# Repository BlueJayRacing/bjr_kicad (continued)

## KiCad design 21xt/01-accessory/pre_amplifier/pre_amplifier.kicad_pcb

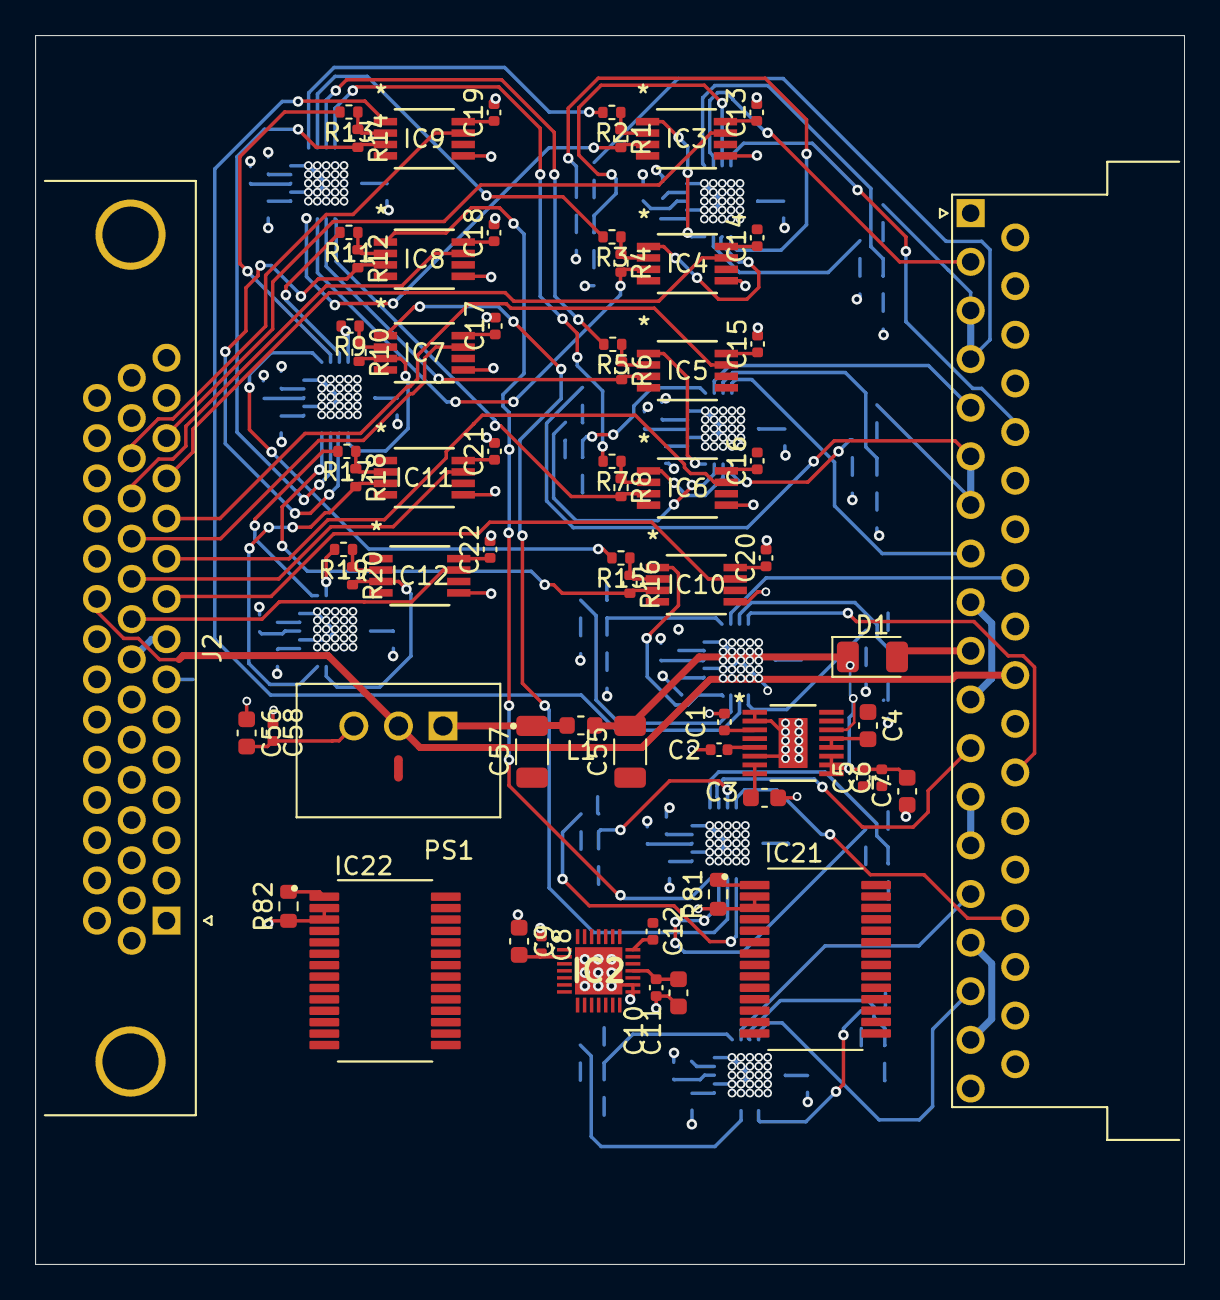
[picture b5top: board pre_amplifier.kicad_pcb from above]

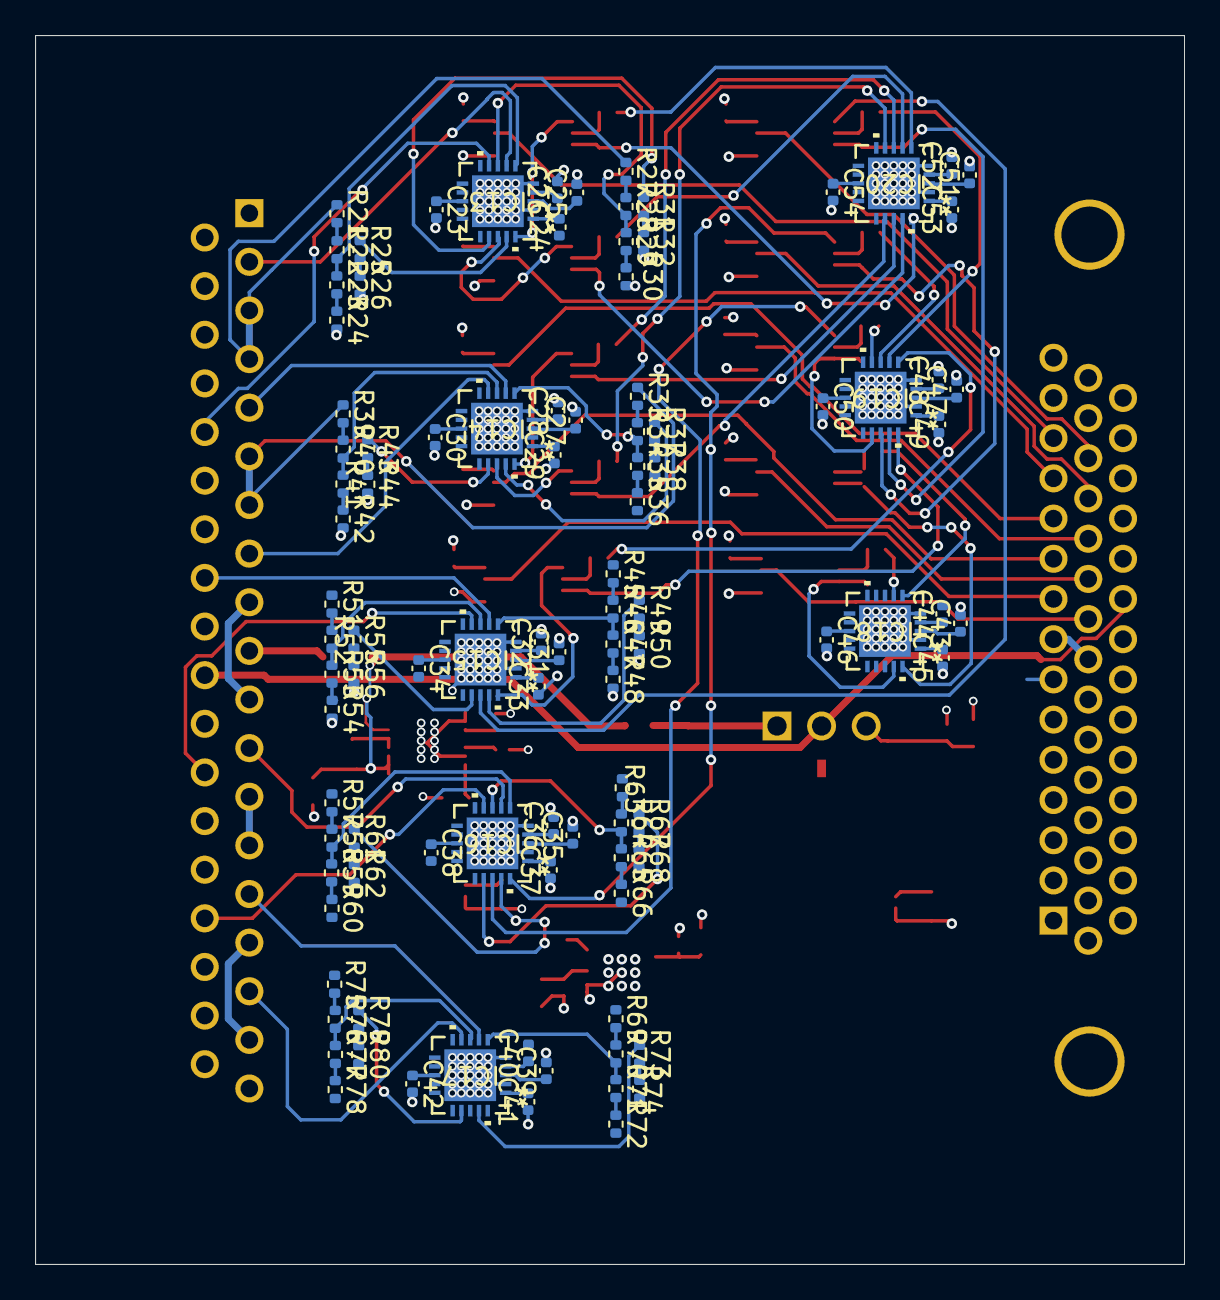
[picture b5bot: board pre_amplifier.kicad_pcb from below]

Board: 4 copper layers, 65.4 x 70.0 mm, 168 parts (100 on the bottom side), 187 nets.

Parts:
C1: 1u; C_0402_1005Metric
C2, C5, C6, C8, C10, C12, C58: 0.1u; C_0402_1005Metric
C3, C4, C7, C9, C11, C56: 10u; C_0603_1608Metric
C13, C14, C15, C16, C17, C18, C19, C20, C21, C22: 0.1uF; C_0402_1005Metric
C23, C26, C28, C30, C32, C34, C36, C38, C40, C42, C44, C46, C48, C50, C52, C54: 1uF; C_0402_1005Metric
C24, C25, C27, C29, C31, C33, C35, C37, C39, C41, C43, C45, C47, C49, C51, C53: 10nF; C_0402_1005Metric
C55, C57: 4.7u; C_1206_3216Metric
D1: D_Schottky; D_1206_3216Metric
IC1: LT6658AHMSE-5#PBF; LT6658AHMSE-2.5-PBF
IC2: AD5679RBCPZ-1; QFN40P400X400X100-29N-D
IC3, IC4, IC5, IC6, IC7, IC8, IC9, IC10, IC11, IC12: INA827AIDGKR
IC13, IC14, IC15, IC16, IC17, IC18, IC19, IC20: MAX14774ATP+; MAX14774ATP_
IC21, IC22: MAX7301AAI+; SOP65P777X199-28N
J1: Conn_02x19_Counter_Clockwise; DSUB-37_Female_Horizontal_P2.77x2.54mm_EdgePinOffset9.40mm
J2: Conn_02x23_Counter_Clockwise; DSUB-44-HD_Female_Horizontal_P2.29x1.98mm_EdgePinOffset3.03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
L1: 10u; L_0603_1608Metric
NT1: NetTie_2; NetTie-2_SMD_Pad0.5mm
PS1: P7805B-500; CONV_P7805B-500
R1, R4, R6, R8, R10, R12, R14, R16, R18, R20: 35; R_0402_1005Metric
R2, R3, R5, R7, R9, R11, R13, R15, R17, R19: R; R_0402_1005Metric
R21, R23, R25, R27, R29, R31, R33, R35, R37, R39, R41, R43, R45, R47, R49, R51, R53, R55, R57, R59, R61, R63, R65, R67, R69, R71, R73, R75, R77, R79: 330; R_0402_1005Metric
R22, R24, R26, R28, R30, R32, R34, R36, R38, R40, R42, R44, R46, R48, R50, R52, R54, R56, R58, R60, R62, R64, R66, R68, R70, R72, R74, R76, R78, R80: 20; R_0402_1005Metric
R81, R82: 39k; R_0603_1608Metric

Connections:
2v5_ref: C12.2, IC2.21 (VREF)
3V3: J2.31, J2.32
5v_buck: C8.2, C9.2, C10.2, C11.2, C23.1, C26.1, C28.1, C30.1, C32.1, C34.1, C36.1, C38.1, C40.1, C42.1, C44.1, C46.1, C48.1, C50.1, C52.1, C54.1, C56.2, C58.2, IC2.2 (VDD), IC2.6 (GAIN), IC2.18 (VLOGIC), IC13.4 (VCC), IC13.13 (VL), IC14.4 (VCC), IC14.13 (VL), IC15.4 (VCC), IC15.13 (VL), IC16.4 (VCC), IC16.13 (VL), IC17.4 (VCC), IC17.13 (VL), IC18.4 (VCC), IC18.13 (VL), IC19.4 (VCC), IC19.13 (VL), IC20.4 (VCC), IC20.13 (VL), IC21.28 (V+), IC22.28 (V+), PS1.3 (+VOUT)
5v_reful: C3.2, C4.2, C13.1, C14.1, C15.1, C16.1, C17.1, C18.1, C19.1, C20.1, C21.1, C22.1, IC1.7 (VOUT2_S), IC1.8 (VOUT2_F), IC1.12 (VOUT1_F), IC1.13 (VOUT1_S), IC3.8 (+VS), IC4.8 (+VS), IC5.8 (+VS), IC6.8 (+VS), IC7.8 (+VS), IC8.8 (+VS), IC9.8 (+VS), IC10.8 (+VS), IC11.8 (+VS), IC12.8 (+VS), J1.3, J1.4, J1.6, J1.7, J1.9, J1.11, J1.13, J1.14, J1.16, J1.18, R21.1, R27.1, R33.1, R39.1, R45.1, R51.1, R57.1, R63.1, R69.1, R75.1
11v1_bat: D1.2 (A), J1.10, J2.8, J2.23
11v1_schott: C5.2, C6.2, C7.2, C55.2, D1.1 (K), IC1.9 (~OD), IC1.10 (VIN2), IC1.11 (VIN1), IC1.14 (VIN), L1.1
!LDAC: IC2.17 (~LDAC), J2.21
!RESET: IC2.20 (~RESET), J2.20
AN1: IC3.7 (VOUT), J2.13
AN2: IC4.7 (VOUT), J2.12
AN3: IC5.7 (VOUT), J2.11
AN4: IC6.7 (VOUT), J2.10
AN5: IC10.7 (VOUT), J2.9
AN6: IC9.7 (VOUT), J2.28
AN7: IC8.7 (VOUT), J2.27
AN8: IC7.7 (VOUT), J2.26
AN9: IC11.7 (VOUT), J2.25
AN10: IC12.7 (VOUT), J2.24
B-: J1.29, J2.39, NT1.2, PS1.2 (GND)
CS_amp: IC21.27 (~CS), J2.22
CS_sg: IC22.27 (~CS), J2.19
DAC_BIAS_1: IC2.28 (VOUT1), IC3.6 (REF)
DAC_BIAS_2: IC2.27 (VOUT2), IC4.6 (REF)
DAC_BIAS_3: IC2.26 (VOUT3), IC5.6 (REF)
DAC_BIAS_4: IC2.10 (VOUT4), IC6.6 (REF)
DAC_BIAS_5: IC2.9 (VOUT5), IC10.6 (REF)
DAC_BIAS_6: IC2.8 (VOUT6), IC9.6 (REF)
DAC_BIAS_7: IC2.7 (VOUT7), IC8.6 (REF)
DAC_BIAS_8: IC2.25 (VOUT8), IC7.6 (REF)
DAC_BIAS_9: IC2.24 (VOUT9), IC11.6 (REF)
DAC_BIAS_10: IC2.23 (VOUT10), IC12.6 (REF)
GND: C1.1, C2.1, C3.1, C4.1, C5.1, C6.1, C7.1, C8.1, C9.1, C10.1, C11.1, C12.1, C13.2, C14.2, C15.2, C16.2, C17.2, C18.2, C19.2, C20.2, C21.2, C22.2, C23.2, C24.1, C25.2, C26.2, C27.2, C28.2, C29.1, C30.2, C31.2, C32.2, C33.1, C34.2, C35.2, C36.2, C37.1, C38.2, C39.2, C40.2, C41.1, C42.2, C43.2, C44.2, C45.1, C46.2, C47.2, C48.2, C49.1, C50.2, C51.2, C52.2, C53.1, C54.2, C55.1, C56.1, C57.1, C58.1, IC1.1 (GND_1), IC1.2 (GND_2), IC1.6 (GND_3), IC1.EPAD (GND_4), IC2.15 (GND_1), IC2.16 (GND_2), IC2.29 (EP), IC3.5 (-VS), IC4.5 (-VS), IC5.5 (-VS), IC6.5 (-VS), IC7.5 (-VS), IC8.5 (-VS), IC9.5 (-VS), IC10.5 (-VS), IC11.5 (-VS), IC12.5 (-VS), IC13.2 (GND_1), IC13.5 (I.C.), IC13.21 (GND_2), IC14.2 (GND_1), IC14.5 (I.C.), IC14.21 (GND_2), IC15.2 (GND_1), IC15.5 (I.C.), IC15.21 (GND_2), IC16.2 (GND_1), IC16.5 (I.C.), IC16.21 (GND_2), IC17.2 (GND_1), IC17.5 (I.C.), IC17.21 (GND_2), IC18.2 (GND_1), IC18.5 (I.C.), IC18.21 (GND_2), IC19.2 (GND_1), IC19.5 (I.C.), IC19.21 (GND_2), IC20.2 (GND_1), IC20.5 (I.C.), IC20.21 (GND_2), IC21.2 (GND_1), IC21.3 (GND_2), IC22.2 (GND_1), IC22.3 (GND_2), NT1.1, R24.2, R26.2, R30.2, R32.2, R36.2, R38.2, R42.2, R44.2, R48.2, R50.2, R54.2, R56.2, R60.2, R62.2, R66.2, R68.2, R72.2, R74.2, R78.2, R80.2, R81.1, R82.1
MISO: IC2.19 (SDO), IC21.4 (DOUT), IC22.4 (DOUT), J2.5
MOSI: IC2.5 (SDI), IC21.26 (DIN), IC22.26 (DIN), J2.6
unnamed: C1.2, IC1.3 (BYPASS)
unnamed: C2.2, IC1.5 (NR)
unnamed: IC3.2 (RG_1), R1.1, R2.1
unnamed: IC4.2 (RG_1), R3.1, R4.1
unnamed: IC5.2 (RG_1), R5.1, R6.1
unnamed: IC6.2 (RG_1), R7.1, R8.1
unnamed: IC7.2 (RG_1), R9.1, R10.1
unnamed: IC8.2 (RG_1), R11.1, R12.1
unnamed: IC9.2 (RG_1), R13.1, R14.1
unnamed: IC10.2 (RG_1), R15.1, R16.1
unnamed: IC11.2 (RG_1), R17.1, R18.1
unnamed: IC12.2 (RG_1), R19.1, R20.1
unnamed: C25.1, IC13.3 (VN)
unnamed: C24.2, IC13.1 (VP)
unnamed: C27.1, IC14.3 (VN)
unnamed: C29.2, IC14.1 (VP)
unnamed: C31.1, IC15.3 (VN)
unnamed: C33.2, IC15.1 (VP)
unnamed: C35.1, IC16.3 (VN)
unnamed: C37.2, IC16.1 (VP)
unnamed: C39.1, IC17.3 (VN)
unnamed: C41.2, IC17.1 (VP)
unnamed: C43.1, IC18.3 (VN)
unnamed: C45.2, IC18.1 (VP)
unnamed: C47.1, IC19.3 (VN)
unnamed: C49.2, IC19.1 (VP)
unnamed: C51.1, IC20.3 (VN)
unnamed: C53.2, IC20.1 (VP)
unnamed: IC21.1 (ISET), R81.2
unnamed: IC22.1 (ISET), R82.2
unnamed: C57.2, L1.2, PS1.1 (+VIN)
unnamed: R21.2, R22.1
unnamed: R23.2, R24.1
unnamed: R25.2, R26.1
unnamed: R27.2, R28.1
unnamed: R29.2, R30.1
unnamed: R31.2, R32.1
unnamed: R33.2, R34.1
unnamed: R35.2, R36.1
unnamed: R37.2, R38.1
unnamed: R39.2, R40.1
unnamed: R41.2, R42.1
unnamed: R43.2, R44.1
unnamed: R45.2, R46.1
unnamed: R47.2, R48.1
unnamed: R49.2, R50.1
unnamed: R51.2, R52.1
unnamed: R53.2, R54.1
unnamed: R55.2, R56.1
unnamed: R57.2, R58.1
unnamed: R59.2, R60.1
unnamed: R61.2, R62.1
unnamed: R63.2, R64.1
unnamed: R65.2, R66.1
unnamed: R67.2, R68.1
unnamed: R69.2, R70.1
unnamed: R71.2, R72.1
unnamed: R73.2, R74.1
unnamed: R75.2, R76.1
unnamed: R77.2, R78.1
unnamed: R79.2, R80.1
P12: IC20.11 (EN1), IC21.5 (P12)
P12_2: IC13.11 (EN1), IC22.5 (P12)
P13: IC20.12 (EN2), IC21.6 (P13)
P13_2: IC13.12 (EN2), IC22.6 (P13)
P14: IC20.14 (EN3), IC21.7 (P14)
P14_2: IC13.14 (EN3), IC22.7 (P14)
P15: IC20.15 (EN4), IC21.8 (P15)
P15_2: IC13.15 (EN4), IC22.8 (P15)
P16: IC19.11 (EN1), IC21.9 (P16)
P16_2: IC14.11 (EN1), IC22.9 (P16)
P17: IC19.12 (EN2), IC21.10 (P17)
P17_2: IC14.12 (EN2), IC22.10 (P17)
P18: IC19.14 (EN3), IC21.11 (P18)
P18_2: IC14.14 (EN3), IC22.11 (P18)
P19: IC19.15 (EN4), IC21.12 (P19)
P19_2: IC14.15 (EN4), IC22.12 (P19)
P20: IC18.11 (EN1), IC21.13 (P20)
P20_2: IC15.11 (EN1), IC22.13 (P20)
P21: IC18.12 (EN2), IC21.14 (P21)
P21_2: IC15.12 (EN2), IC22.14 (P21)
P22_2: IC15.14 (EN3), IC22.15 (P22)
P23_2: IC15.15 (EN4), IC22.16 (P23)
P24_2: IC16.11 (EN1), IC22.17 (P24)
P25_2: IC16.12 (EN2), IC22.18 (P25)
P26_2: IC16.14 (EN3), IC22.19 (P26)
P27_2: IC16.15 (EN4), IC22.20 (P27)
P28_2: IC17.11 (EN1), IC22.21 (P28)
P29_2: IC17.12 (EN2), IC22.22 (P29)
P30_2: IC17.14 (EN3), IC22.23 (P30)
P31_2: IC17.15 (EN4), IC22.24 (P31)
QS1F-: IC13.7 (A2), J1.2
QS2F-: IC13.9 (A4), J1.24
QS3F-: IC14.7 (A2), J1.5
QS4F-: IC14.9 (A4), J1.8
QS5F-: IC15.7 (A2), J1.27
QS6F-: IC15.9 (A4), J1.31
QS7F-: IC16.7 (A2), J1.12
QS8F-: IC16.9 (A4), J1.34
QS9F-: IC17.7 (A2), J1.15
QS10F-: IC17.9 (A4), J1.17
Rg1_y: IC20.6 (A1), R2.2
Rg1_z: IC3.3 (RG_2), IC20.20 (B1), R1.2
Rg2_y: IC20.7 (A2), R3.2
Rg2_z: IC4.3 (RG_2), IC20.19 (B2), R4.2
Rg3_y: IC20.8 (A3), R5.2
Rg3_z: IC5.3 (RG_2), IC20.18 (B3), R6.2
Rg4_y: IC20.9 (A4), R7.2
Rg4_z: IC6.3 (RG_2), IC20.17 (B4), R8.2
Rg5_y: IC19.6 (A1), R15.2
Rg5_z: IC10.3 (RG_2), IC19.20 (B1), R16.2
Rg6_y: IC19.7 (A2), R13.2
Rg6_z: IC9.3 (RG_2), IC19.19 (B2), R14.2
Rg7_y: IC19.8 (A3), R11.2
Rg7_z: IC8.3 (RG_2), IC19.18 (B3), R12.2
Rg8_y: IC19.9 (A4), R9.2
Rg8_z: IC7.3 (RG_2), IC19.17 (B4), R10.2
Rg9_y: IC18.6 (A1), R17.2
Rg9_z: IC11.3 (RG_2), IC18.20 (B1), R18.2
Rg10_y: IC18.7 (A2), R19.2
Rg10_z: IC12.3 (RG_2), IC18.19 (B2), R20.2
SCLK: IC2.4 (SCLK), J2.7
SLCK: IC21.25 (SCLK), IC22.25 (SCLK)
Switch_x1: IC13.6 (A1), R22.2, R23.1
Switch_x3: IC13.8 (A3), R28.2, R29.1
Switch_x5: IC14.6 (A1), R34.2, R35.1
Switch_x7: IC14.8 (A3), R40.2, R41.1
Switch_x9: IC15.6 (A1), R46.2, R47.1
Switch_x11: IC15.8 (A3), R52.2, R53.1
Switch_x13: IC16.6 (A1), R58.2, R59.1
Switch_x15: IC16.8 (A3), R64.2, R65.1
Switch_x17: IC17.6 (A1), R70.2, R71.1
Switch_x19: IC17.8 (A3), R76.2, R77.1
Switch_y1: IC3.1 (-IN), IC13.20 (B1)
Switch_y2: IC13.19 (B2), R25.1
Switch_y3: IC4.1 (-IN), IC13.18 (B3)
Switch_y4: IC13.17 (B4), R31.1
Switch_y5: IC5.1 (-IN), IC14.20 (B1)
Switch_y6: IC14.19 (B2), R37.1
Switch_y7: IC6.1 (-IN), IC14.18 (B3)
Switch_y8: IC14.17 (B4), R43.1
Switch_y9: IC10.1 (-IN), IC15.20 (B1)
Switch_y10: IC15.19 (B2), R49.1
Switch_y11: IC9.1 (-IN), IC15.18 (B3)
Switch_y12: IC15.17 (B4), R55.1
Switch_y13: IC8.1 (-IN), IC16.20 (B1)
Switch_y14: IC16.19 (B2), R61.1
Switch_y15: IC7.1 (-IN), IC16.18 (B3)
Switch_y16: IC16.17 (B4), R67.1
Switch_y17: IC11.1 (-IN), IC17.20 (B1)
Switch_y18: IC17.19 (B2), R73.1
Switch_y19: IC12.1 (-IN), IC17.18 (B3)
Switch_y20: IC17.17 (B4), R79.1

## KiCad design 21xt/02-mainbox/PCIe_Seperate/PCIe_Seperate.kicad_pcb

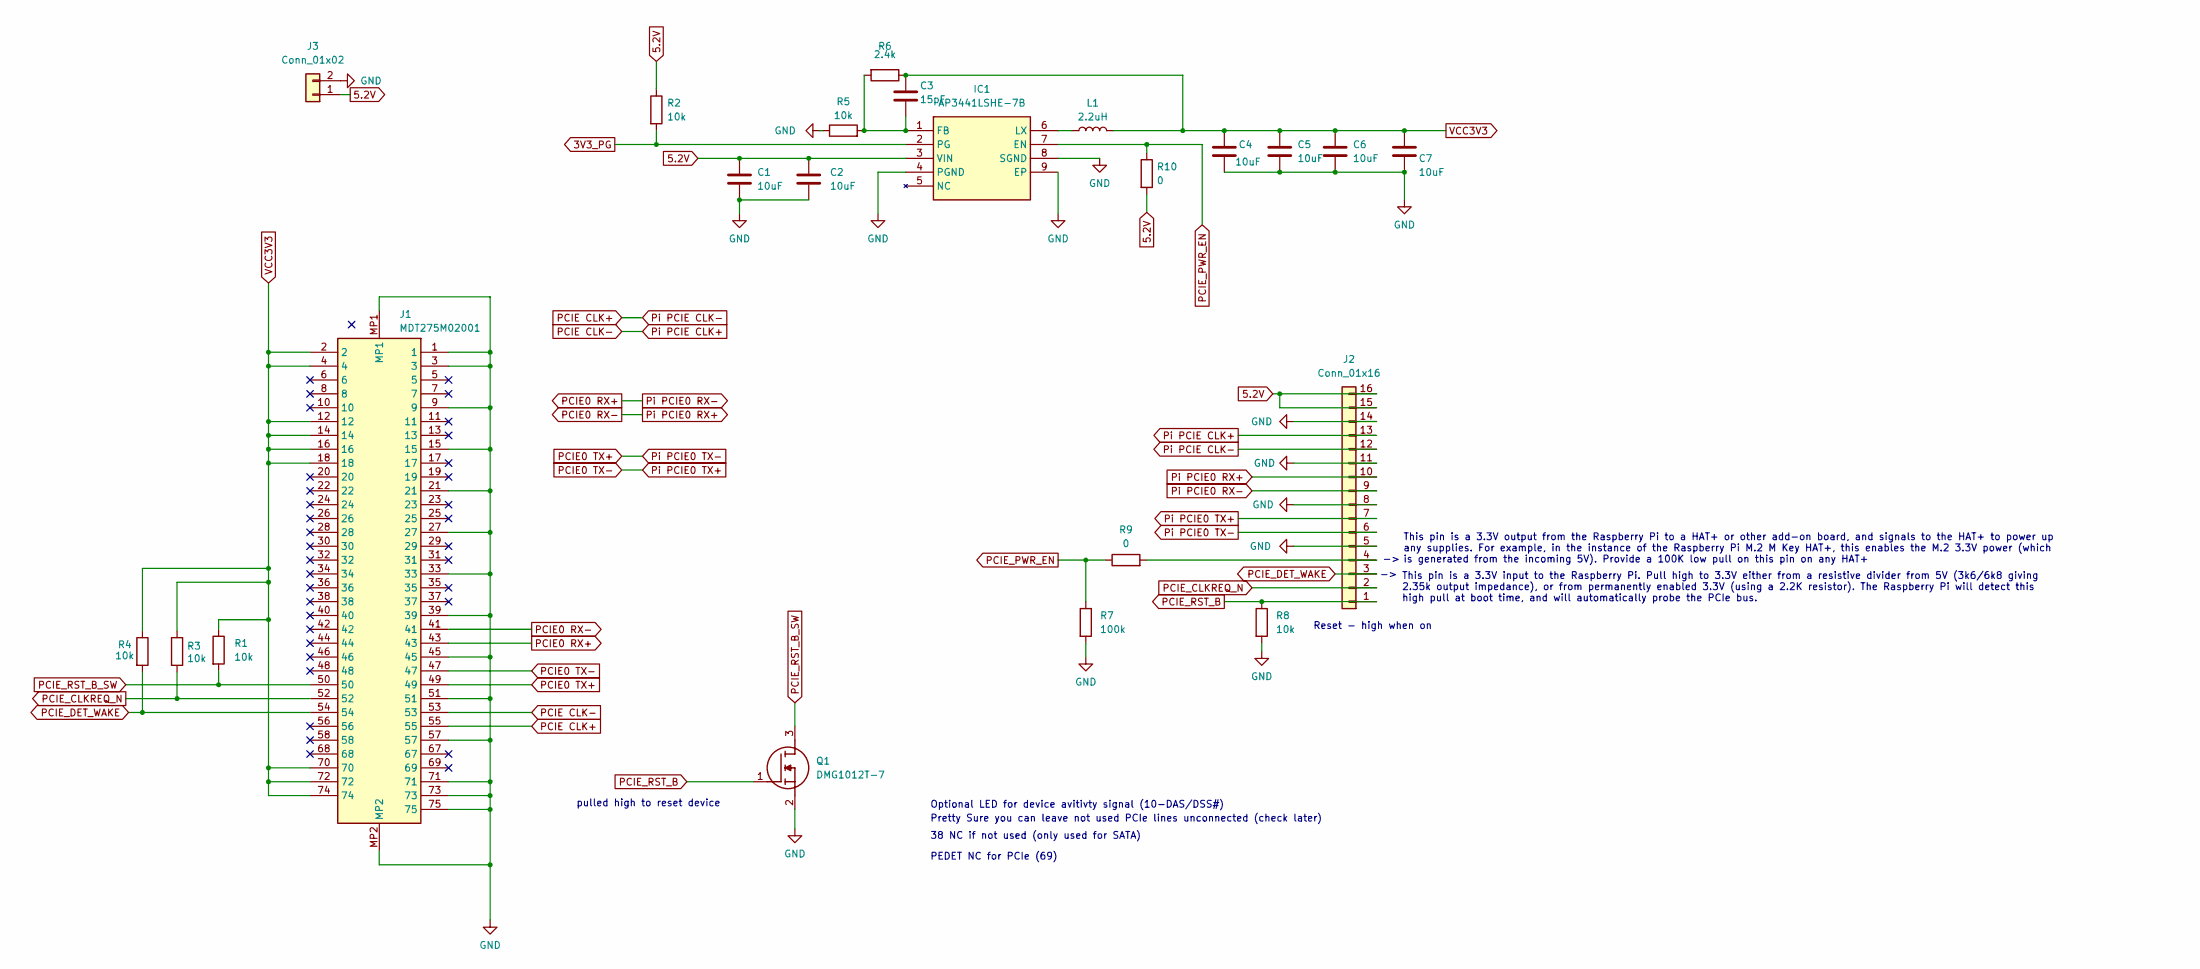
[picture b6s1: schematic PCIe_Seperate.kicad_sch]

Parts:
C1, C2, C4, C5, C6, C7: 10uF; C_0402_1005Metric
C3: 15pF; C_0402_1005Metric
IC1: AP3441LSHE-7B; AP3441LSHE7B; Mouser Part Number 621-AP3441LSHE-7B
J1: MDT275M02001; Mouser Part Number 523-MDT275M02001
J2: Conn_01x16; ZF5S1601TWT (p3)
J3: Conn_01x02; JST_VH_B2PS-VH_1x02_P3.96mm_Horizontal (--)
L1: 2.2uH; L_1008_2520Metric
Q1: DMG1012T-7; SOT50P160X90-3N(DIODE); Mouser Part Number 621-DMG1012T-7
R1, R2, R3, R4, R5, R8: 10k; R_0402_1005Metric
R6: 2.4k; R_0402_1005Metric
R7: 100k; R_0402_1005Metric
R9, R10: 0; R_0402_1005Metric

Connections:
3V3_PG: IC1.2 (PG), R2.2
5.2V: C1.1, C2.1, IC1.3 (VIN), J2.15, J2.16, J3.1, R2.1, R10.2
GND: C1.2, C2.2, C4.2, C5.2, C6.2, C7.2, IC1.4 (PGND), IC1.8 (SGND), IC1.9 (EP), J1.1, J1.3, J1.9, J1.15, J1.21, J1.27, J1.33, J1.39, J1.45, J1.51, J1.57, J1.71, J1.73, J1.75, J1.MP1, J1.MP2, J2.5, J2.8, J2.11, J2.14, J3.2, Q1.2 (S), R5.1, R7.2, R8.2
unnamed: C3.2, IC1.1 (FB), R5.2, R6.2
unnamed: IC1.6 (LX), L1.1
unnamed: J2.4, R9.2
PCIE0 RX+: J1.43, J2.9
PCIE0 RX-: J1.41, J2.10
PCIE0 TX+: J1.49, J2.6
PCIE0 TX-: J1.47, J2.7
PCIE CLK+: J1.55, J2.12
PCIE CLK-: J1.53, J2.13
PCIE_CLKREQ_N: J1.52, J2.2, R3.2
PCIE_DET_WAKE: J1.54, J2.3, R4.2
PCIE_PWR_EN: IC1.7 (EN), R7.1, R9.1, R10.1
PCIE_RST_B: J2.1, Q1.1 (G), R8.1
PCIE_RST_B_SW: J1.50, Q1.3 (D), R1.2
VCC3V3: C3.1, C4.1, C5.1, C6.1, C7.1, J1.2, J1.4, J1.12, J1.14, J1.16, J1.18, J1.70, J1.72, J1.74, L1.2, R1.1, R3.1, R4.1, R6.1

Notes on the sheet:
Reset - high when on
This pin is a 3.3V input to the Raspberry Pi. Pull high to 3.3V either from a resistive divider from 5V (3k6/6k8 giving 2.35k output impedance), or from permanently enabled 3.3V (using a 2.2K resistor). The Raspberry Pi will detect this high pull at boot time, and will automatically probe the PCIe 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
PEDET NC for PCIe (69)
This pin is a 3.3V output from the Raspberry Pi to a HAT+ or other add-on board, and signals to the HAT+ to power up any supplies. For example, in the instance of the Raspberry Pi M.2 M Key HAT+, this enables the M.2 3.3V power (which is generated from the incoming 5V). Provide a 100K low pull on t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
Optional LED for device avitivty signal (10-DAS/DSS#)
38 NC if not used (only used for SATA)
pulled high to reset device
Pretty Sure you can leave not used PCIe lines unconnected (check later)

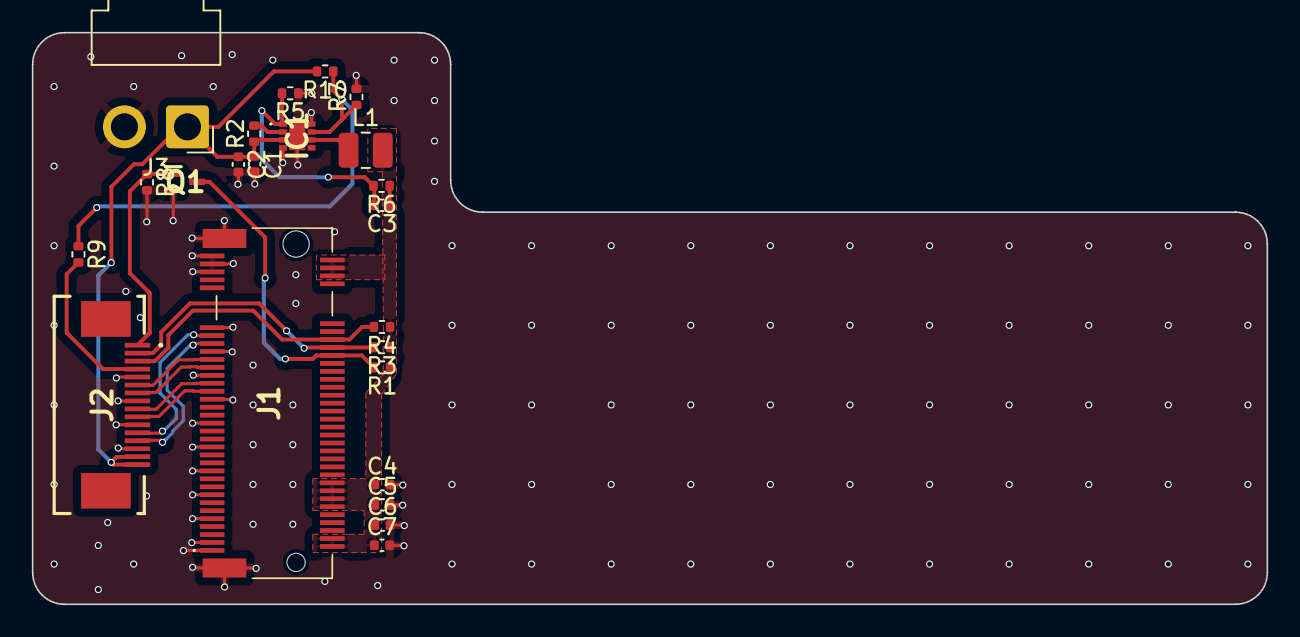
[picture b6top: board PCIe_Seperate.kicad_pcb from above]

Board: 4 copper layers, 77.6 x 35.9 mm, 23 parts (0 on the bottom side), 18 nets.

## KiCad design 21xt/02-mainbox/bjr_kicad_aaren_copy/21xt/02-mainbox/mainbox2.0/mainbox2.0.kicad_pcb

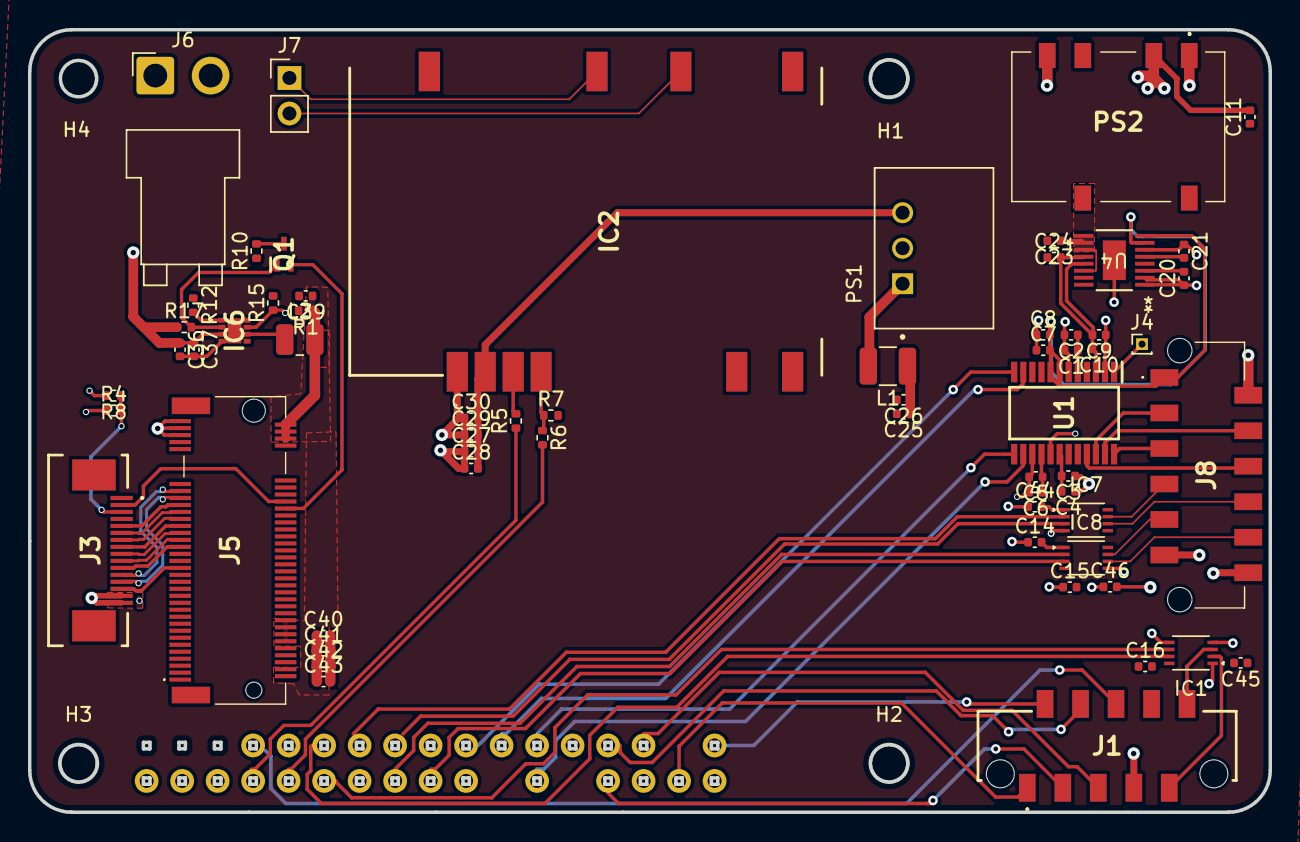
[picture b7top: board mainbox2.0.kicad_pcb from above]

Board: 4 copper layers, 88.8 x 56.0 mm, 68 parts (1 on the bottom side), 63 nets.

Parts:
C1, C3, C5, C7, C10, C11, C14, C15, C16, C20, C21, C23, C27, C44, C45, C46: 0.1uF; C_0402_1005Metric
C2, C4, C8, C24: 1uF; C_0402_1005Metric
C6, C9, C25, C28, C36, C37, C40, C41, C42, C43: 10uF; C_0402_1005Metric
C26: 4.7uF; C_0402_1005Metric
C29: 47pF; C_0402_1005Metric
C30: 8.2pF; C_0402_1005Metric
C39: 15pF; C_0402_1005Metric
H1, H2, H3, H4: MountingHole; MountingHole_2.5mm
IC1, IC7, IC8: SN74LVC2T45DCTTG4; VSSOP-8_2.4x2.1mm_P0.5mm
IC2: XBP9X-DMUS-011; RLS397
IC6: AP3441LSHE-7B; AP3441LSHE7B
J1: Conn_01x10; 908160010
J3: Conn_01x16; ZF5S1601TWT
J4: Conn_01x01_Pin; PinHeader_1x01_P1.00mm_Vertical
J5: MDT275M02001
J6: Conn_01x02; JST_VH_B2PS-VH_1x02_P3.96mm_Horizontal
J7: Conn_01x02; PinHeader_1x02_P2.54mm_Vertical
J8: Conn_01x12; 908160012
J10: Conn_02x20_Odd_Even; PinHeader_2x20_P2.54mm_Vertical
L1: 3.9uH; L_1210_3225Metric
L2: 2.2uH; L_1008_2520Metric
PS1: R-78B3.3-1.5L; CONV_R-78B3.3-1.5
PS2: R2D12-0509; R2D120509
Q1: DMG1012T-7; SOT50P160X90-3N
R1, R17: 10k; R_0402_1005Metric
R4: 3k6; R_0402_1005Metric
R5, R6: 68; R_0402_1005Metric
R7, R15: 100k; R_0402_1005Metric
R8: 6k8; R_0402_1005Metric
R10: 33; R_0402_1005Metric
R12: 45k; R_0402_1005Metric
U1: AD7175-2BRUZ; SOP65P640X120-24N
U4: LT6658AHMSE-5-PBF; LT6658AHMSE-2.5-PBF

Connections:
3V3: C5.1, C6.1, C14.2, C16.2, C44.2, IC1.8 (VCCB), IC7.1 (VCCA), IC8.1 (VCCA), J10.17, R7.2, U1.16 (IOVDD)
3V3_PG: IC6.2 (PG), Q1.1 (G), R17.2
3V3_XBEE: C27.2, C28.2, C29.2, C30.2, IC2.2 (VCC), PS1.3 (+VOUT)
5.2V: C11.2, C15.2, C25.1, C26.1, C36.1, C37.1, C45.2, C46.2, IC1.1 (VCCA), IC6.3 (VIN), IC7.8 (VCCB), IC8.8 (VCCB), J1.7, J6.2, J8.11, J10.2, J10.4, L1.1, PS2.2 (+VIN), R17.1
5VADC/SENSOR: C7.2, C8.2, J8.1, U1.7 (AVDD1), U1.8 (AVDD2), U4.7 (VOUT2_S), U4.8 (VOUT2_F)
5VRAIL: J3.15, J3.16, R4.1
5VRef: C9.2, C10.2, C24.2, U1.3 (REF+), U4.12 (VOUT1_F), U4.13 (VOUT1_S)
9V: C23.1, PS2.7 (+VOUT), U4.9 (*OD), U4.10 (VIN2), U4.11 (VIN1), U4.14 (VIN)
ADC_SPI_DIN: J10.19, U1.12 (DIN)
ADC_SPI_DOUT: J10.21, U1.11 (DOUT/*RDY)
AIN0: J8.6, U1.21 (AIN0)
AIN1: J8.3, U1.22 (AIN1)
AIN2: J8.4, U1.23 (AIN2)
AIN3: J8.5, U1.24 (AIN3)
AIN4: J4.1, U1.1 (AIN4)
DIGITAL_INPUT_1: IC8.6 (B2), J8.10
DIGITAL_INPUT_2: IC8.7 (B1), J8.9
DIGITAL_INPUT_3: IC7.6 (B2), J8.8
DIGITAL_INPUT_4: IC7.7 (B1), J8.7
DIGITAL_OUTPUT_1: IC8.3 (A2), J10.18
DIGITAL_OUTPUT_2: IC8.2 (A1), J10.16
DIGITAL_OUTPUT_3: IC7.3 (A2), J10.15
DIGITAL_OUTPUT_4: IC7.2 (A1), J10.13
DINXBee: IC2.4 (DIN/DIO14/~CONFIG), R6.1, R7.1
DOUTXBee: IC2.3 (DIO13/DOUT), R5.2
GNDA: C1.2, C2.2, C5.2, C6.2, C7.1, C8.1, C9.1, C10.1, C20.1, C21.1, C23.2, C24.1, J8.2, U1.2 (REF-), U1.6 (AVSS), U4.1 (GND), U4.2 (GND), U4.6 (GND), U4.EPAD
GNDD: C3.1, C4.1, C11.1, C14.1, C15.1, C16.1, C25.2, C26.2, C27.1, C28.1, C29.1, C30.1, C44.1, C45.1, C46.1, IC1.4 (GND), IC1.5 (DIR), IC2.1 (GND_1), IC2.11 (GND_2), IC2.13 (GND_3), IC2.22 (GND_4), IC2.35 (GND_5), IC7.4 (GND), IC7.5 (DIR), IC8.4 (GND), IC8.5 (DIR), J1.8, J6.1, J8.12, J10.6, J10.9, J10.14, J10.20, J10.25, J10.30, J10.34, PS1.2 (GND), PS2.1 (-VIN), PS2.5 (-VOUT), U1.15 (*SYNC/*ERROR), U1.17 (DGND)
GNDS: C36.2, C37.2, C40.2, C41.2, C42.2, C43.2, IC6.4 (PGND), IC6.8 (SGND), IC6.9 (EP), J3.1, J3.5, J3.8, J3.11, J3.14, J5.1, J5.3, J5.9, J5.15, J5.21, J5.27, J5.33, J5.39, J5.45, J5.51, J5.57, J5.71, J5.73, J5.75, J5.MP1, J5.MP2, R8.2, R10.1, R12.1, R15.2
IN1(3.3V): IC1.7 (B1), J10.11
IN1(5V): IC1.2 (A1), J1.9
IN2(3.3V): IC1.6 (B2), J10.12
IN2(5V): IC1.3 (A2), J1.10
NAVIN: J1.2, J10.33
NAVOUT: J1.1, J10.32
unnamed: IC2.29 (DIO6/~RTS), J7.1
unnamed: IC2.26 (DIO9/ON/~SLEEP), J7.2
unnamed: C39.2, IC6.1 (FB), R1.2, R12.2
unnamed: IC6.6 (LX), L2.1
unnamed: J10.8, R5.1
unnamed: J10.10, R6.2
unnamed: L1.2, PS1.1 (+VIN)
unnamed: C1.1, C2.1, U1.5 (REGCAPA)
unnamed: C3.2, C4.2, U1.18 (REGCAPD)
unnamed: C20.2, U4.3 (BYPASS)
unnamed: C21.2, U4.5 (NR)
PCIE0 RX+: J3.9, J5.43
PCIE0 RX-: J3.10, J5.41
PCIE0 TX+: J3.6, J5.49
PCIE0 TX-: J3.7, J5.47
PCIE CLK+: J3.12, J5.55
PCIE CLK-: J3.13, J5.53
PCIE_CLKREQ_N: J3.2, J5.52
PCIE_DET_WAKE: J3.3, R4.2, R8.1
PCIE_PWR_EN: IC6.7 (EN), J3.4, R15.1
PCIE_RST_B: Q1.3 (D), R10.2
PCIE_RST_B_SW: J5.50, Q1.2 (S)
POWER_BOARD_PORT_RXD: J1.3, J10.28
POWER_BOARD_PORT_TXD: J1.4, J10.27
RPi_SPI_CS: J10.24, U1.14 (*CS)
SCLK: J10.23, U1.13 (SCLK)
STEERING_WHEEL_PORT_RXD: J1.5, J10.29
STEERING_WHEEL_PORT_TXD: J1.6, J10.7
VCC3V3: C39.1, C40.1, C41.1, C42.1, C43.1, J5.2, J5.4, J5.12, J5.14, J5.16, J5.18, J5.70, J5.72, J5.74, L2.2, R1.1
